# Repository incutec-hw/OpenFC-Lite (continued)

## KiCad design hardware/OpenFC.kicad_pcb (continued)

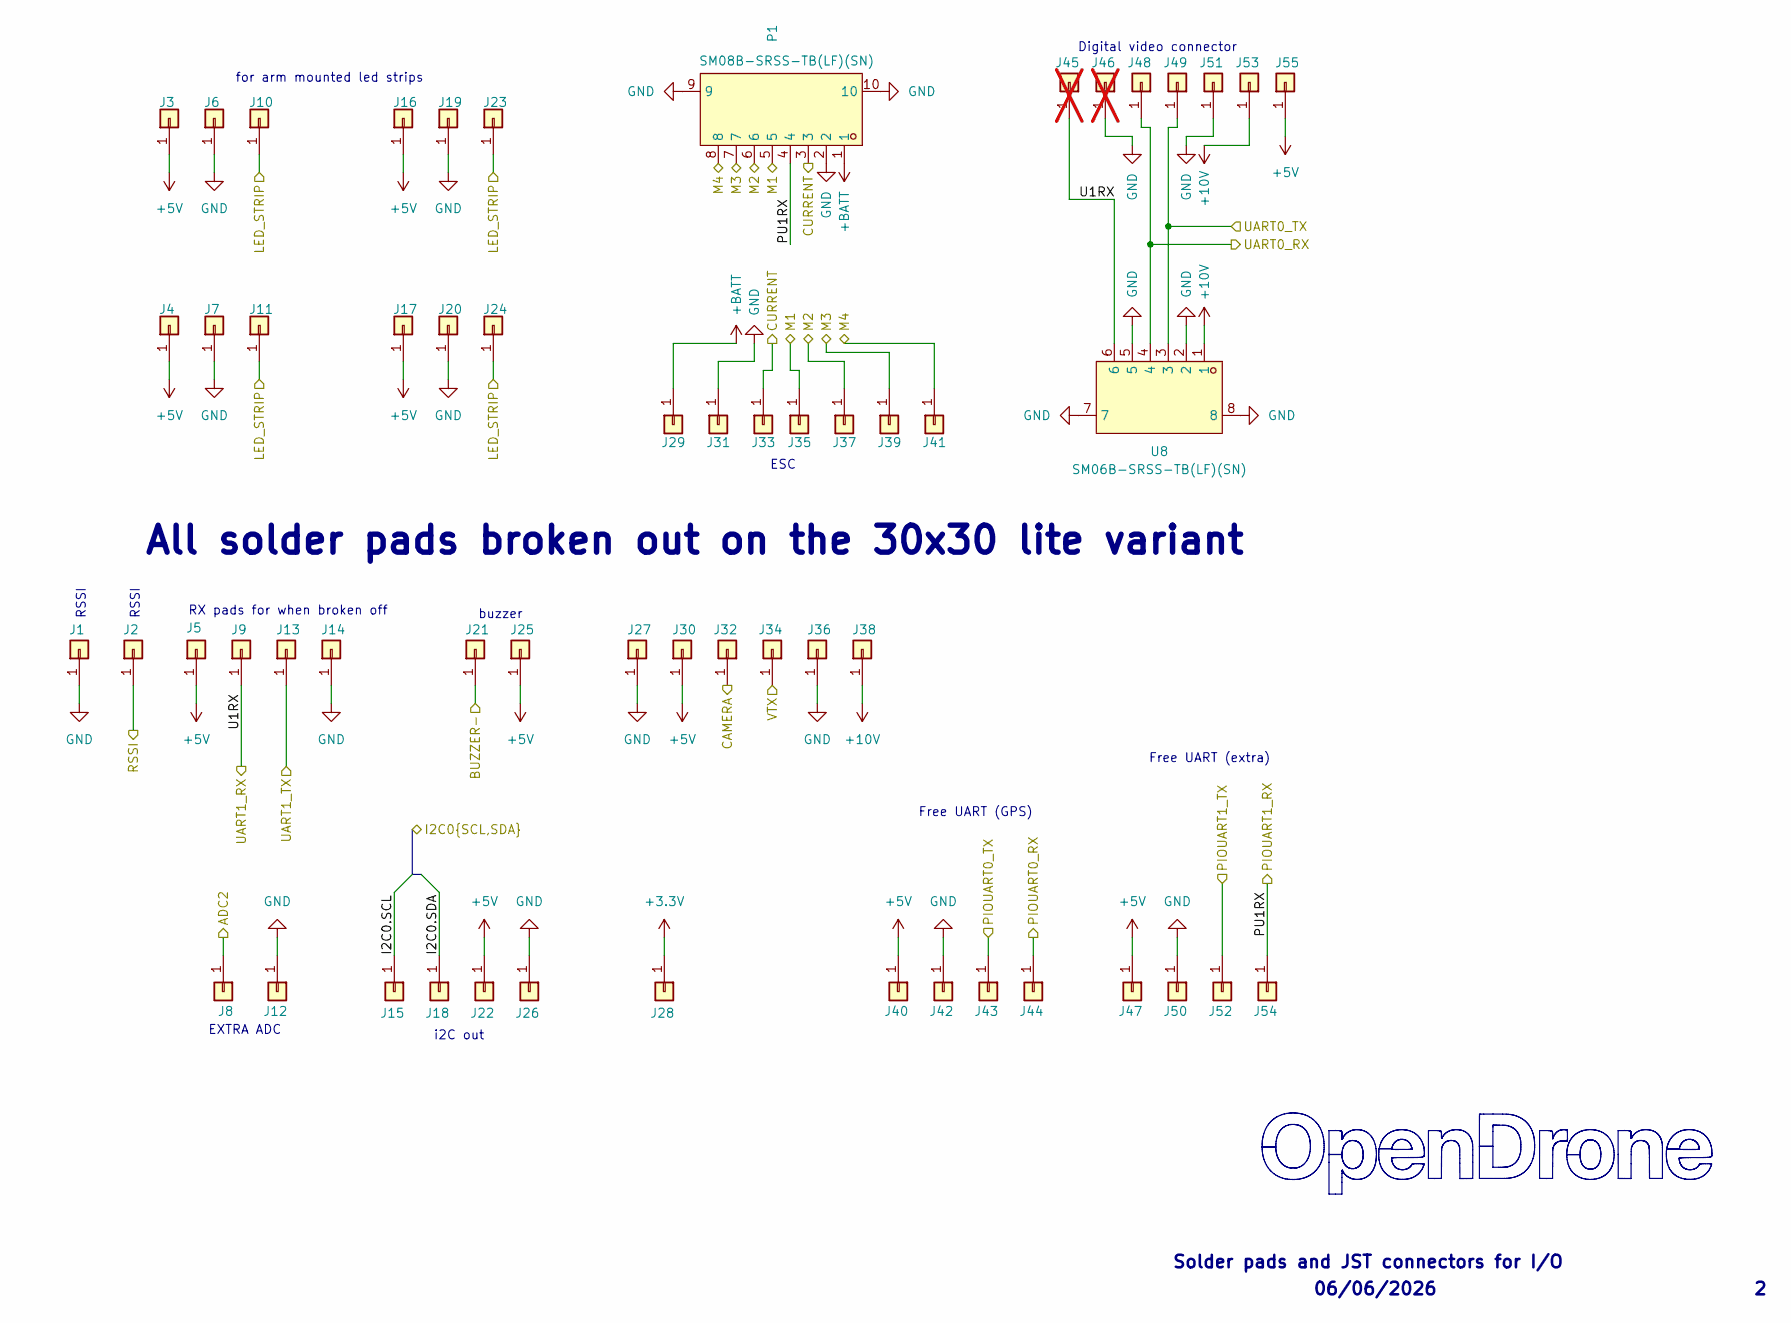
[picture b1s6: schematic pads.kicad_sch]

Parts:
J1, J2, J3, J4, J5, J6, J7, J8, J9, J10, J11, J12, J13, J14, J15, J16, J17, J18, J19, J20, J21, J22, J23, J24, J25, J26, J27, J28, J29, J30, J31, J32, J33, J34, J35, J36, J37, J38, J39, J40, J41, J42, J43, J44, J47, J48, J49, J50, J51, J52, J53, J54, J55: 5V; small_pad
J45, J46: 5V; small_pad; not fitted
P1: SM08B-SRSS-TB(LF)(SN); CONN-TH_SM08B-SRSS-TB-LF-SN; MPN SM08B-SRSS-TB(LF)(SN); LCSC C160407
U8: SM06B-SRSS-TB(LF)(SN); CONN-SMD_SM06B-SRSS-TB-LF-SN; MPN SM06B-SRSS-TB(LF)(SN); LCSC C160405

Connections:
+3.3V: J28.1 (Pin_1_1); also elsewhere on the board
+5V: J3.1 (Pin_1_1), J4.1 (Pin_1_1), J5.1 (Pin_1_1), J16.1 (Pin_1_1), J17.1 (Pin_1_1), J22.1 (Pin_1_1), J25.1 (Pin_1_1), J30.1 (Pin_1_1), J40.1 (Pin_1_1), J47.1 (Pin_1_1), J55.1 (Pin_1_1); also elsewhere on the board
+10V: J38.1 (Pin_1_1), J53.1 (Pin_1_1), U8.1; also elsewhere on the board
+BATT: J29.1 (Pin_1_1), P1.1; also elsewhere on the board
/OSD/VIDEO_IN: J32.1 (Pin_1_1); also elsewhere on the board
/OSD/VIDEO_OUT: J34.1 (Pin_1_1); also elsewhere on the board
/PADS/ADC2: J8.1 (Pin_1_1); also elsewhere on the board
/PADS/BUZZER-: J21.1 (Pin_1_1); also elsewhere on the board
/PADS/CURRENT: J33.1 (Pin_1_1), P1.3; also elsewhere on the board
/PADS/I2C0.SCL: J15.1 (Pin_1_1); also elsewhere on the board
/PADS/I2C0.SDA: J18.1 (Pin_1_1); also elsewhere on the board
/PADS/LED_STRIP: J10.1 (Pin_1_1), J11.1 (Pin_1_1), J23.1 (Pin_1_1), J24.1 (Pin_1_1); also elsewhere on the board
/PADS/M1: J35.1 (Pin_1_1), P1.5; also elsewhere on the board
/PADS/M2: J37.1 (Pin_1_1), P1.6; also elsewhere on the board
/PADS/M3: J39.1 (Pin_1_1), P1.7; also elsewhere on the board
/PADS/M4: J41.1 (Pin_1_1), P1.8; also elsewhere on the board
/PADS/PIOUART0_RX: J44.1 (Pin_1_1); also elsewhere on the board
/PADS/PIOUART0_TX: J43.1 (Pin_1_1); also elsewhere on the board
/PADS/PIOUART1_TX: J52.1 (Pin_1_1); also elsewhere on the board
/PADS/PU1RX: J54.1 (Pin_1_1), P1.4; also elsewhere on the board
/PADS/RSSI: J2.1 (Pin_1_1); also elsewhere on the board
/PADS/U1RX: J9.1 (Pin_1_1), J45.1, U8.6; also elsewhere on the board
/PADS/UART0_RX: J48.1 (Pin_1_1), U8.4; also elsewhere on the board
/PADS/UART0_TX: J49.1 (Pin_1_1), U8.3; also elsewhere on the board
/PADS/UART1_TX: J13.1 (Pin_1_1); also elsewhere on the board
GND: J1.1 (Pin_1_1), J6.1 (Pin_1_1), J7.1 (Pin_1_1), J12.1 (Pin_1_1), J14.1 (Pin_1_1), J19.1 (Pin_1_1), J20.1 (Pin_1_1), J26.1 (Pin_1_1), J27.1 (Pin_1_1), J31.1 (Pin_1_1), J36.1 (Pin_1_1), J42.1 (Pin_1_1), J46.1, J50.1 (Pin_1_1), J51.1 (Pin_1_1), P1.2, P1.9, P1.10, U8.2, U8.5, U8.7, U8.8; also elsewhere on the board

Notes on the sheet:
06/06/2026
RSSI
Free UART (GPS)
Solder pads and JST connectors for I/O
i2C out
All solder pads broken out on the 30x30 lite variant
Free UART (extra)
buzzer
RX pads for when broken off
ESC
Digital video connector
EXTRA ADC
for arm mounted led strips

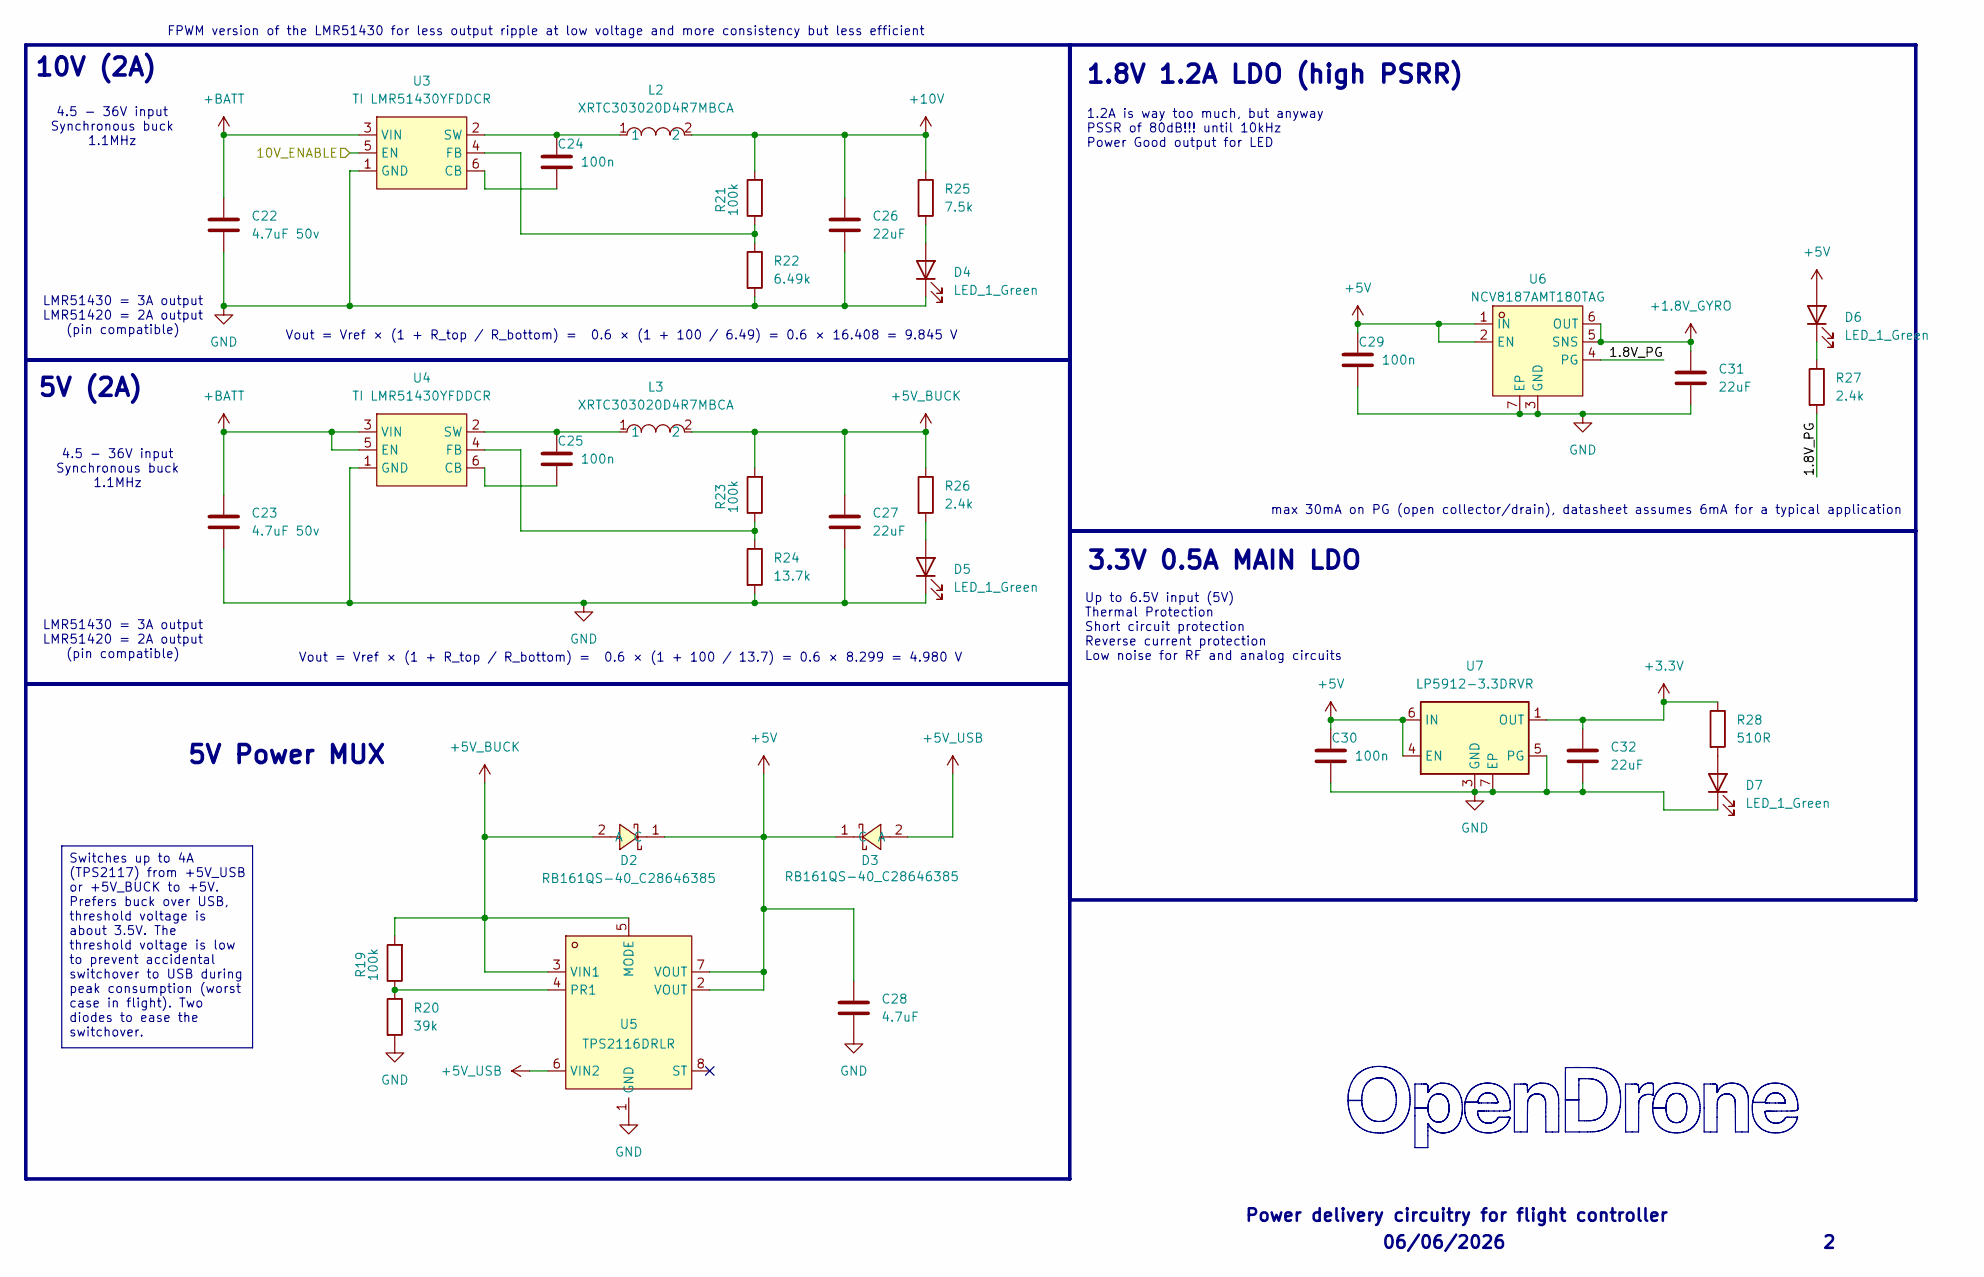
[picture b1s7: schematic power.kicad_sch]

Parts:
C22, C23: 4.7uF 50v; C_0805_2012Metric; MPN CL21A475KBQNNNE; LCSC C98192
C24, C25, C29, C30: 100n; C_0201_0603Metric; MPN GRM033R61E104KE14D; LCSC C76939
C26, C27: 22uF; C_0603_1608Metric; MPN CL10A226MO7JZNC; LCSC C2762594
C28: 4.7uF; C_0402_1005Metric; MPN CL05A475MP5NRNC; LCSC C23733
C31, C32: 22uF; C_0402_1005Metric; MPN CL05A226MQ5QUNC; LCSC C105226
D2, D3: RB161QS-40_C28646385; SOD-882_L1.0-W0.6-RD; MPN RB161QS-40; LCSC C28646385
D4, D5, D6, D7: LED_1_Green; LED_0402_1005Metric; MPN XL-1005UGC; LCSC C965793
L2, L3: XRTC303020D4R7MBCA; IND-SMD_L3.0-W3.0_AFE303020S; MPN XRTC303020D4R7MBCA; LCSC C39846837
R19, R21, R23: 100k; R_0201_0603Metric; MPN 0201WMF1003TEE; LCSC C270364
R20: 39k; R_0201_0603Metric; MPN 0201WMF3902TEE; LCSC C473053
R22: 6.49k; R_0201_0603Metric; LCSC C2107920
R24: 13.7k; R_0201_0603Metric; MPN RC-01W1372FT; LCSC C320695
R25: 7.5k; R_0201_0603Metric; LCSC C474437
R26, R27: 2.4k; R_0201_0603Metric; LCSC C166281
R28: 510R; R_0201_0603Metric; LCSC C57784
U3, U4: TI LMR51430YFDDCR; SOT-23-6_L2.9-W1.6-P0.95-LS2.9-BL; MPN TI LMR51430YFDDCR; LCSC C5219261
U5: TPS2116DRLR; SOT-583-8_L2.1-W1.6-P0.50-LS1.6-BL; MPN TPS2116DRLR; LCSC C3235557
U6: NCV8187AMT180TAG; WDFN-6_L2.0-W2.0-P0.65-BL-EP; MPN NCV8187AMT180TAG; LCSC C893189
U7: LP5912-3.3DRVR; WSON-6-1EP_2x2mm_P0.65mm_EP1x1.6mm; MPN LP5912-3.3DRVR; LCSC C524780

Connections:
+1.8V_GYRO: C31.1, U6.5 (SNS), U6.6 (OUT); also elsewhere on the board
+3.3V: C32.1, R28.1, U7.1 (OUT); also elsewhere on the board
+5V: C28.1, C29.1, C30.1, D2.1 (C), D3.1 (C), D6.2 (A), U5.2 (VOUT), U5.7 (VOUT), U6.1 (IN), U6.2 (EN), U7.4 (EN), U7.6 (IN); also elsewhere on the board
+5V_BUCK: C27.1, D2.2 (A), L3.2, R19.2, R23.2, R26.1, U5.3 (VIN1), U5.5 (MODE)
+5V_USB: D3.2 (A), U5.6 (VIN2); also elsewhere on the board
+10V: C26.1, L2.2, R21.2, R25.1; also elsewhere on the board
+BATT: C22.1, C23.1, U3.3 (VIN), U4.3 (VIN), U4.5 (EN); also elsewhere on the board
/POWER/1.8V_PG: R27.2, U6.4 (PG)
/POWER/10V_ENABLE: U3.5 (EN); also elsewhere on the board
GND: C22.2, C23.2, C26.2, C27.2, C28.2, C29.2, C30.2, C31.2, C32.2, D4.1 (K), D5.1 (K), D7.1 (K), R20.2, R22.2, R24.2, U3.1 (GND), U4.1 (GND), U5.1 (GND), U6.3 (GND), U6.7 (EP), U7.3 (GND), U7.5 (PG), U7.7 (EP); also elsewhere on the board
unnamed: D4.2 (A), R25.2
unnamed: D5.2 (A), R26.2
unnamed: D6.1 (K), R27.1
unnamed: D7.2 (A), R28.2
unnamed: C24.2, U3.6 (CB)
unnamed: R21.1, R22.1, U3.4 (FB)
unnamed: C24.1, L2.1, U3.2 (SW)
unnamed: C25.2, U4.6 (CB)
unnamed: R23.1, R24.1, U4.4 (FB)
unnamed: C25.1, L3.1, U4.2 (SW)
unnamed: R19.1, R20.1, U5.4 (PR1)

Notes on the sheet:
5V Power MUX
1.2A is way too much, but anyway PSSR of 80dB!!! until 10kHz Power Good output for LED
max 30mA on PG (open collector/drain), datasheet assumes 6mA for a typical application
4.5 - 36V input Synchronous buck 1.1MHz
Power delivery circuitry for flight controller
06/06/2026
LMR51430 = 3A output LMR51420 = 2A output (pin compatible)
Vout = Vref × (1 + R_top / R_bottom) = 0.6 × (1 + 100 / 6.49) = 0.6 × 16.408 = 9.845 V
Vout = Vref × (1 + R_top / R_bottom) = 0.6 × (1 + 100 / 13.7) = 0.6 × 8.299 = 4.980 V
Up to 6.5V input (5V) Thermal Protection Short circuit protection Reverse current protection Low noise for RF and analog circuits
5V (2A)
1.8V 1.2A LDO (high PSRR)
FPWM version of the LMR51430 for less output ripple at low voltage and more consistency but less efficient
10V (2A)
3.3V 0.5A MAIN LDO
Switches up to 4A (TPS2117) from +5V_USB or +5V_BUCK to +5V. Prefers buck over USB, threshold voltage is about 3.5V. The threshold voltage is low to prevent accidental switchover to USB during peak consumption (worst case in flight). Two diodes to ease the switchover.

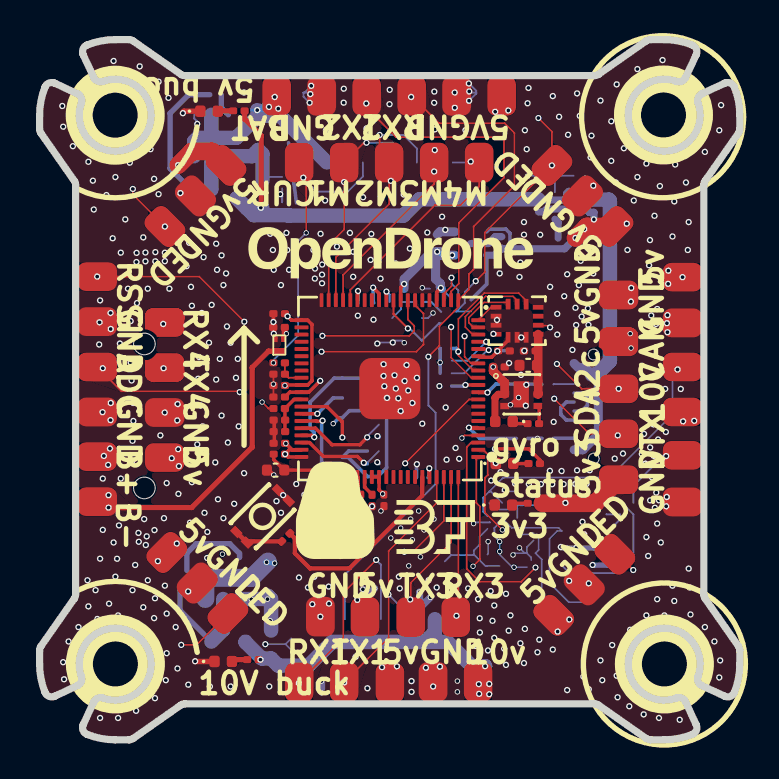
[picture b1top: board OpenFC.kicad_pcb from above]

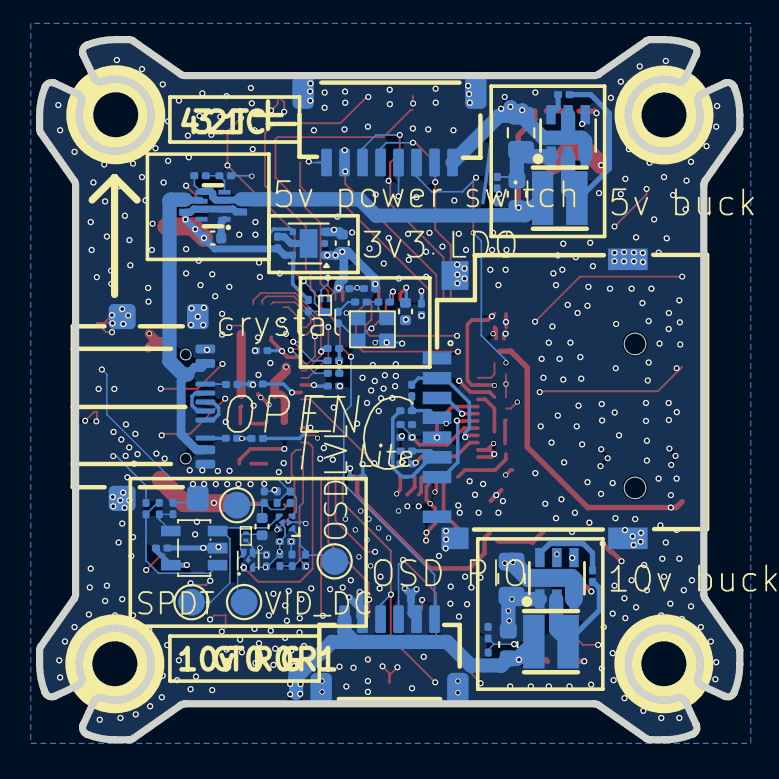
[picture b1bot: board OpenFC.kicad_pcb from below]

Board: 6 copper layers, 38.9 x 38.9 mm, 165 parts (74 on the bottom side), 84 nets.

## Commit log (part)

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2026-06-03 move changes from mini over to "maxi"
2026-06-04 rev2 update
2026-06-04 lite done
2026-06-05 routing
2026-06-06 reinsert resistor that kicad randomly deleted
2026-06-06 BF connector standard logo
    https://betaflight.com/docs/development/manufacturer/connector-standard
2026-06-06 cleanup
